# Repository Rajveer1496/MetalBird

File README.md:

# Current State of Project

### Flight Controller PCB:

<div align="center">

**Top Layer**

<table border="0" cellspacing="0" cellpadding="10">
  <tr>
    <td align="center">
      
    </td>
    <td align="center">
      
    </td>
  </tr>
</table>

---

**Bottom Layer**

<table border="0" cellspacing="0" cellpadding="10">
  <tr>
    <td align="center">
      
    </td>
    <td align="center">
      
    </td>
  </tr>
</table>

---

### Flight Controller Schematic:

</div>

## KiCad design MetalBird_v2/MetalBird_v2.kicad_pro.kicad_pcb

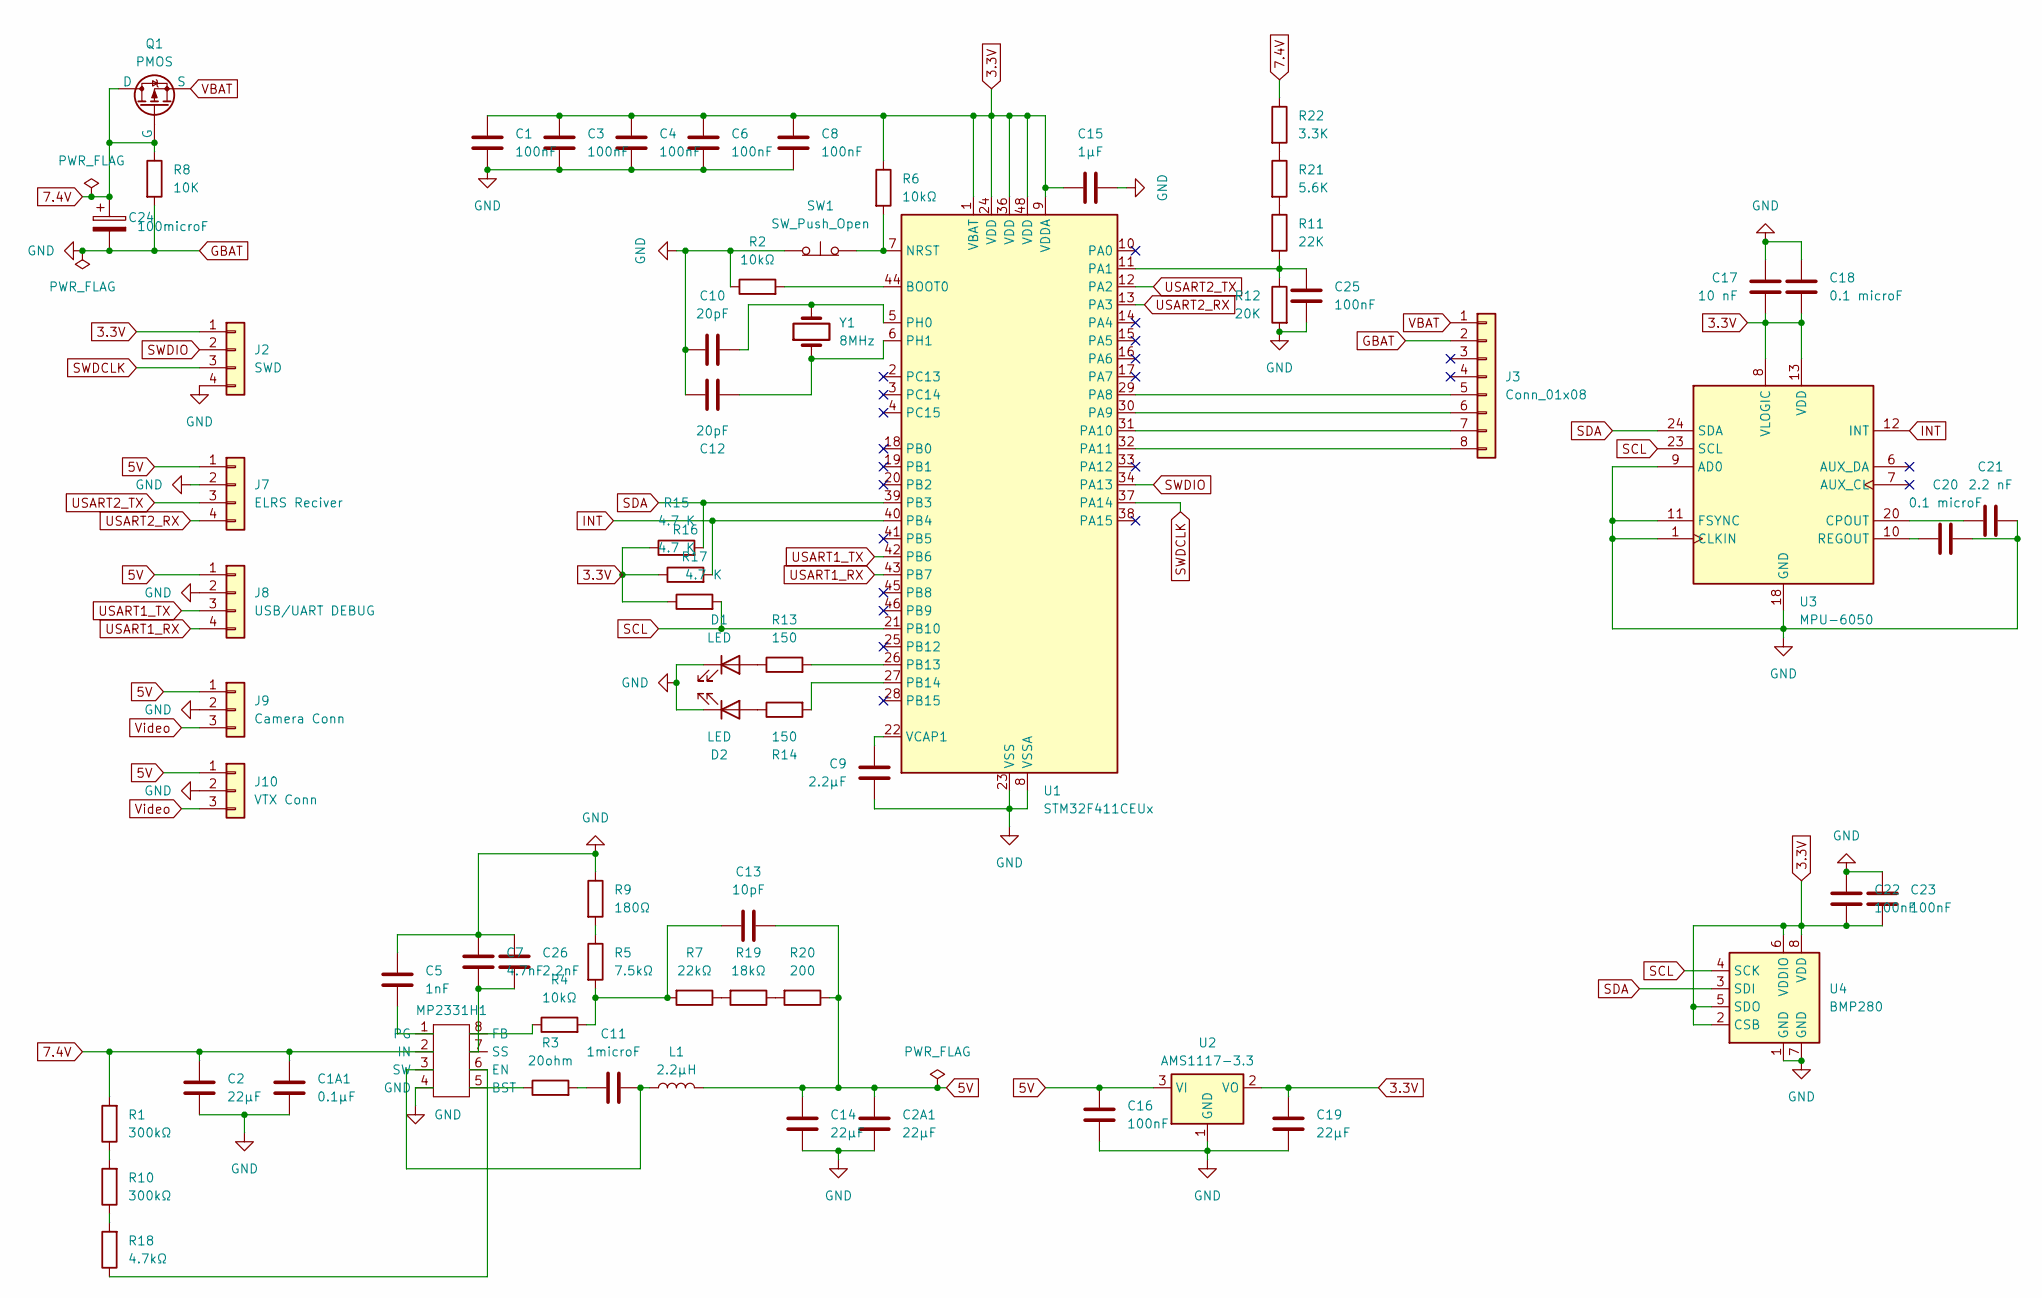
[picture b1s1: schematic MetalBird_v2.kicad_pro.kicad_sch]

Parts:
C1, C3, C4, C6, C8, C16, C22, C23, C25: 100nF; C_0603_1608Metric
C1A1: 0.1µF; C_0603_1608Metric
C2, C2A1, C14, C19: 22µF; C_1206_3216Metric
C5: 1nF; C_0603_1608Metric
C7: 4.7nF; C_0603_1608Metric
C9: 2.2μF; C_0603_1608Metric
C10, C12: 20pF; C_0603_1608Metric
C11: 1microF; C_0603_1608Metric
C13: 10pF; C_0603_1608Metric
C15: 1μF; C_0603_1608Metric
C17: 10 nF; C_0603_1608Metric
C18, C20: 0.1 microF; C_0603_1608Metric
C21: 2.2 nF; C_0603_1608Metric
C24: 100microF; C_1206_3216Metric
C26: 2.2nF; C_0603_1608Metric
D1, D2: LED; LED_0603_1608Metric
J2: SWD; PinHeader_1x04_P2.54mm_Vertical
J3: Conn_01x08; JST_SH_BM08B-SRSS-TB_1x08-1MP_P1.00mm_Vertical
J7: ELRS Reciver; PinHeader_1x04_P2.54mm_Vertical
J8: USB/UART DEBUG; PinHeader_1x04_P2.54mm_Vertical
J9: Camera Conn; PinHeader_1x03_P2.54mm_Vertical
J10: VTX Conn; PinHeader_1x03_P2.54mm_Vertical
L1: 2.2µH; L_Cenker_CKCS4018
MP2331H1: SOT-583-8
Q1: PMOS; SOT-23
R1, R10: 300kΩ; R_0603_1608Metric
R2, R4, R6: 10kΩ; R_0603_1608Metric
R3: 20ohm; R_0603_1608Metric
R5: 7.5kΩ; R_0603_1608Metric
R7: 22kΩ; R_0603_1608Metric
R8: 10K; R_0603_1608Metric
R9: 180Ω; R_0603_1608Metric
R11: 22K; R_0603_1608Metric
R12: 20K; R_0603_1608Metric
R13, R14: 150; R_0603_1608Metric
R15, R16, R17: 4.7 K; R_0603_1608Metric
R18: 4.7kΩ; R_0603_1608Metric
R19: 18kΩ; R_0603_1608Metric
R20: 200; R_0603_1608Metric
R21: 5.6K; R_0603_1608Metric
R22: 3.3K; R_0603_1608Metric
SW1: SW_Push_Open; SW_SPST_PTS645Sx43SMTR92
U1: STM32F411CEUx; QFN-48-1EP_7x7mm_P0.5mm_EP5.6x5.6mm
U2: AMS1117-3.3; SOT-223-3_TabPin2
U3: MPU-6050; InvenSense_QFN-24_4x4mm_P0.5mm
U4: BMP280; Bosch_LGA-8_2x2.5mm_P0.65mm_ClockwisePinNumbering
Y1: 8MHz; Crystal_SMD_3225-4Pin_3.2x2.5mm

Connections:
3.3V: C1.1, C3.1, C4.1, C6.1, C8.1, C15.2, C17.2, C18.2, C19.1, C22.1, C23.1, J2.1, R6.1, R15.1, R16.1, R17.1, U1.1 (VBAT), U1.9 (VDDA), U1.24 (VDD), U1.36 (VDD), U1.48 (VDD), U2.2 (VO), U3.8 (VLOGIC), U3.13 (VDD), U4.2 (CSB), U4.5 (SDO), U4.6 (VDDIO), U4.8 (VDD)
5V: C2A1.1, C13.2, C14.1, C16.1, J7.1, J8.1, J9.1, J10.1, L1.2, R20.1, U2.3 (VI)
7.4V: C1A1.2, C2.2, C24.1, MP2331H1.2 (IN), Q1.1 (D), Q1.2 (G), R1.2, R8.1, R22.1
GBAT: C1.2, C1A1.1, C2.1, C2A1.2, C3.2, C4.2, C5.2, C6.2, C7.2, C8.2, C9.2, C10.1, C12.1, C14.2, C15.1, C16.2, C17.1, C18.1, C19.2, C20.2, C21.2, C22.2, C23.2, C24.2, C25.2, C26.2, D1.1 (K), D2.1 (K), J2.4, J3.2, J7.2, J8.2, J9.2, J10.2, MP2331H1.4 (GND), R2.1, R8.2, R9.1, R12.2, SW1.1 (A), U1.8 (VSSA), U1.23 (VSS), U1.35 (VSS), U1.47 (VSS), U1.49 (VSS), U2.1 (GND), U3.1 (CLKIN), U3.9 (AD0), U3.11 (FSYNC), U3.18 (GND), U4.1 (GND), U4.7 (GND)
INT: R16.2, U1.40 (PB4), U3.12 (INT)
unnamed: C11.1, R3.2
unnamed: C13.1, R4.2, R5.2, R7.2
unnamed: D1.2 (A), R13.1
unnamed: D2.2 (A), R14.1
unnamed: J3.5, U1.29 (PA8)
unnamed: J3.6, U1.30 (PA9)
unnamed: J3.7, U1.31 (PA10)
unnamed: J3.8, U1.32 (PA11)
unnamed: MP2331H1.5 (BST), R3.1
unnamed: MP2331H1.6 (EN), R18.1
unnamed: MP2331H1.8 (FB), R4.1
unnamed: C5.1, MP2331H1.1 (PG)
unnamed: C7.1, C26.1, MP2331H1.7 (SS)
unnamed: C11.2, L1.1, MP2331H1.3 (SW)
unnamed: R1.1, R10.2
unnamed: R5.1, R9.2
unnamed: R10.1, R18.2
unnamed: R11.1, R21.2
unnamed: R19.1, R20.2
unnamed: R7.1, R19.2
unnamed: R21.1, R22.2
unnamed: R6.2, SW1.2 (B), U1.7 (NRST)
unnamed: R2.2, U1.44 (BOOT0)
unnamed: C25.1, R11.2, R12.1, U1.11 (PA1)
unnamed: R13.2, U1.26 (PB13)
unnamed: R14.2, U1.27 (PB14)
unnamed: C10.2, U1.5 (PH0), Y1.2
unnamed: C12.2, U1.6 (PH1), Y1.1
unnamed: C9.1, U1.22 (VCAP1)
unnamed: C21.1, U3.20 (CPOUT)
unnamed: C20.1, U3.10 (REGOUT)
SCL: R17.2, U1.21 (PB10), U3.23 (SCL), U4.4 (SCK)
SDA: R15.2, U1.39 (PB3), U3.24 (SDA), U4.3 (SDI)
SWDCLK: J2.3, U1.37 (PA14)
SWDIO: J2.2, U1.34 (PA13)
USART1_RX: J8.4, U1.43 (PB7)
USART1_TX: J8.3, U1.42 (PB6)
USART2_RX: J7.4, U1.13 (PA3)
USART2_TX: J7.3, U1.12 (PA2)
VBAT: J3.1, Q1.3 (S)
Video: J9.3, J10.3

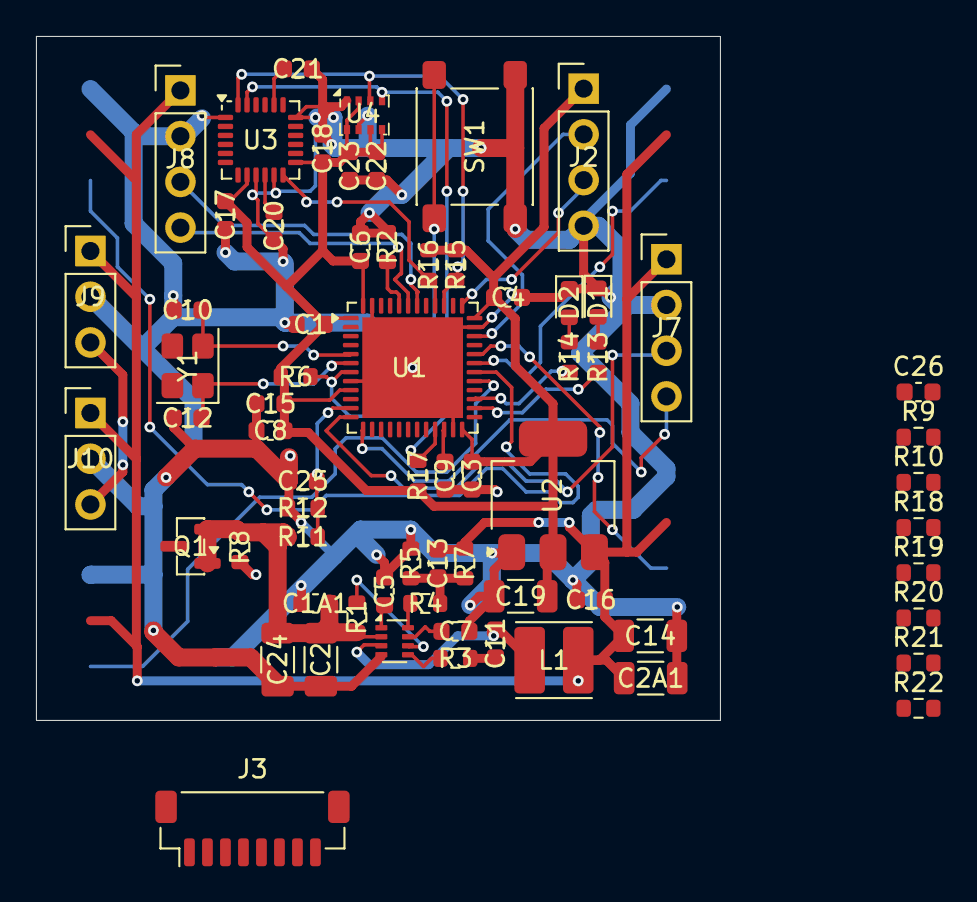
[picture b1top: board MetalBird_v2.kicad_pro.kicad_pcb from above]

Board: 2 copper layers, 38.0 x 38.0 mm, 67 parts (0 on the bottom side), 46 nets.

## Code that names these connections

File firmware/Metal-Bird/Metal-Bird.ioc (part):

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Mcu.Name=STM32F411C(C-E)Ux
Mcu.Package=UFQFPN48
Mcu.UserName=STM32F411CEUx
PB13.GPIOParameters=GPIO_Label
PB13.GPIO_Label=LED_2
PB13.Signal=GPIO_Output
PB14.GPIOParameters=GPIO_Label
PB14.GPIO_Label=LED_1
PB14.Signal=GPIO_Output
PH0\ -\ OSC_IN.Mode=HSE-External-Oscillator
PH0\ -\ OSC_IN.Signal=RCC_OSC_IN
PH1\ -\ OSC_OUT.Mode=HSE-External-Oscillator
PH1\ -\ OSC_OUT.Signal=RCC_OSC_OUT
RCC.HSE_VALUE=8000000
RCC.SYSCLKFreq_VALUE=100000000
RCC.SYSCLKSource=RCC_SYSCLKSOURCE_PLLCLK
board=custom

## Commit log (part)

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2026-02-26 Early Schematic
    Schematic currently has:
    + All power components connected (with coupling capacitors and pull up/ pull down resistors)
    + 8MHz Oscillator
2026-02-26 Current Status of Project
    + Schematic diagram of Flight controller
2026-03-02 MP2331H Buck converter Symbol
    Created own MP2331H symbol as per its manual.
2026-03-03 Buck Converter Setup (7.4 V -> 5.4 V)
    Values of resistors, capacitors, inductors calculated by taking reference from manual.
    Manual: https://www.monolithicpower.com/en/documentview/productdocument/index/version/2/document_type/Datasheet/lang/en/sku/MP2331HGTL-Z/
2026-03-04 LDO setup
2026-03-06 IMU Schematic
    + LDO decoupling capacitor
2026-05-21 IMU Complete
    Used MPU-6050 Product specification datasheet for reference
2026-05-22 Flight Controller Schematic Complete
2026-05-24 Assign Footprints to components
2026-05-25 PCB Design
    laid out all the components in 36x36mm board
2026-05-26 Routing Complete
    - yet to fix cosmetic stuff (silk overlap)
2026-05-27 Gerber files and components list
2026-05-27 Update Status
2026-06-03 Simulate Buck-converter
    Simulated in MPSmart
    + Perfectly takes 7.4V input and outputs 5V
2026-06-04 Capacitor and Resistors to standard values
    By arranging multiple caps and resistors in parallel in series
2026-06-08 Redesign: 4 in 1 ESC
    - yet to route traces
2026-06-22 Buck Converter change
